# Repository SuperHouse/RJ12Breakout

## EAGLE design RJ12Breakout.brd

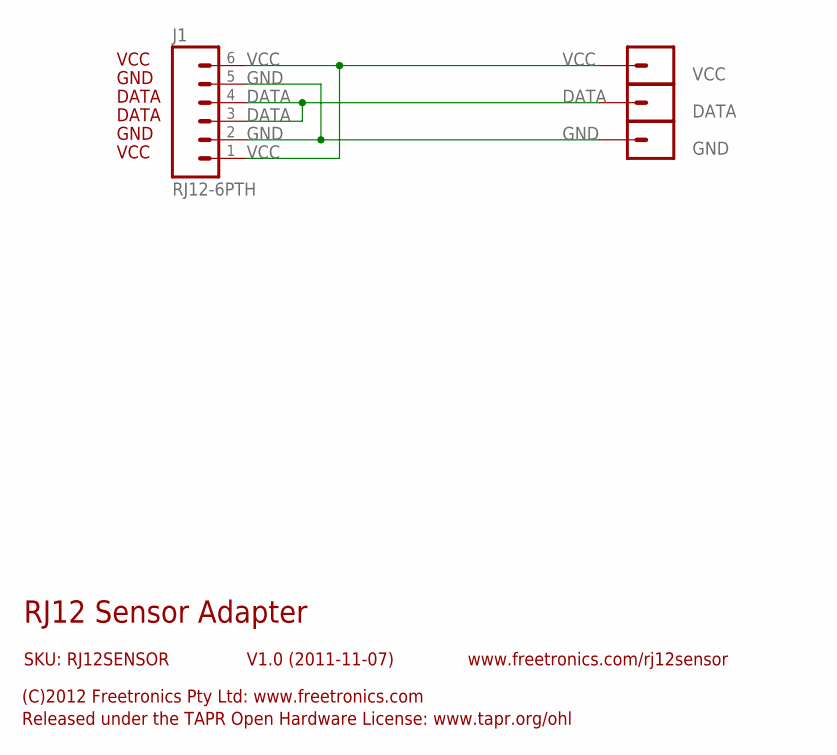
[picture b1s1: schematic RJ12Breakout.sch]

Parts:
DATA: M01PTH; 1X01
GND: M01PTH; 1X01
J1: RJ12-6PTH; RJ12-6
VCC: M01PTH; 1X01

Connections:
DATA: DATA.1, J1.3, J1.4
GND: GND.1, J1.2, J1.5
VCC: J1.1, J1.6, VCC.1

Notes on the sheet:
RJ12 Sensor Adapter
V1.0 (2011-11-07)
SKU: RJ12SENSOR
(C)2012 Freetronics Pty Ltd: www.freetronics.com
Released under the TAPR Open Hardware License: www.tapr.org/ohl
www.freetronics.com/rj12sensor
VCC
DATA
GND

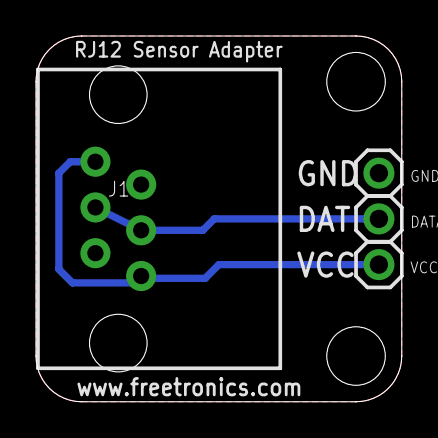
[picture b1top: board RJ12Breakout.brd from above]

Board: 2 copper layers, 20.3 x 20.3 mm, 4 parts (0 on the bottom side), 3 nets.

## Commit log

2019-04-24 Imported old project files
